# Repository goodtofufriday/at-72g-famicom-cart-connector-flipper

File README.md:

at-72g famicom cart connector flipper

for famiclones with the board labled at-72g. probably useable in similar famiclones.

If youre looking here i imagine you know how to mod consoles so i wont go through the how to.

this system doesnt connect expansion audio, so i added through hole pins for pin 45 and 46 so that you can easily re-enable it. 

i havent tested this. but it should work. measurements are "super close". it may need a need shaving. unless its super off im not going to update this design. 

feel free to use the library. it is a full famiclone cart connector library for eagle that i made.

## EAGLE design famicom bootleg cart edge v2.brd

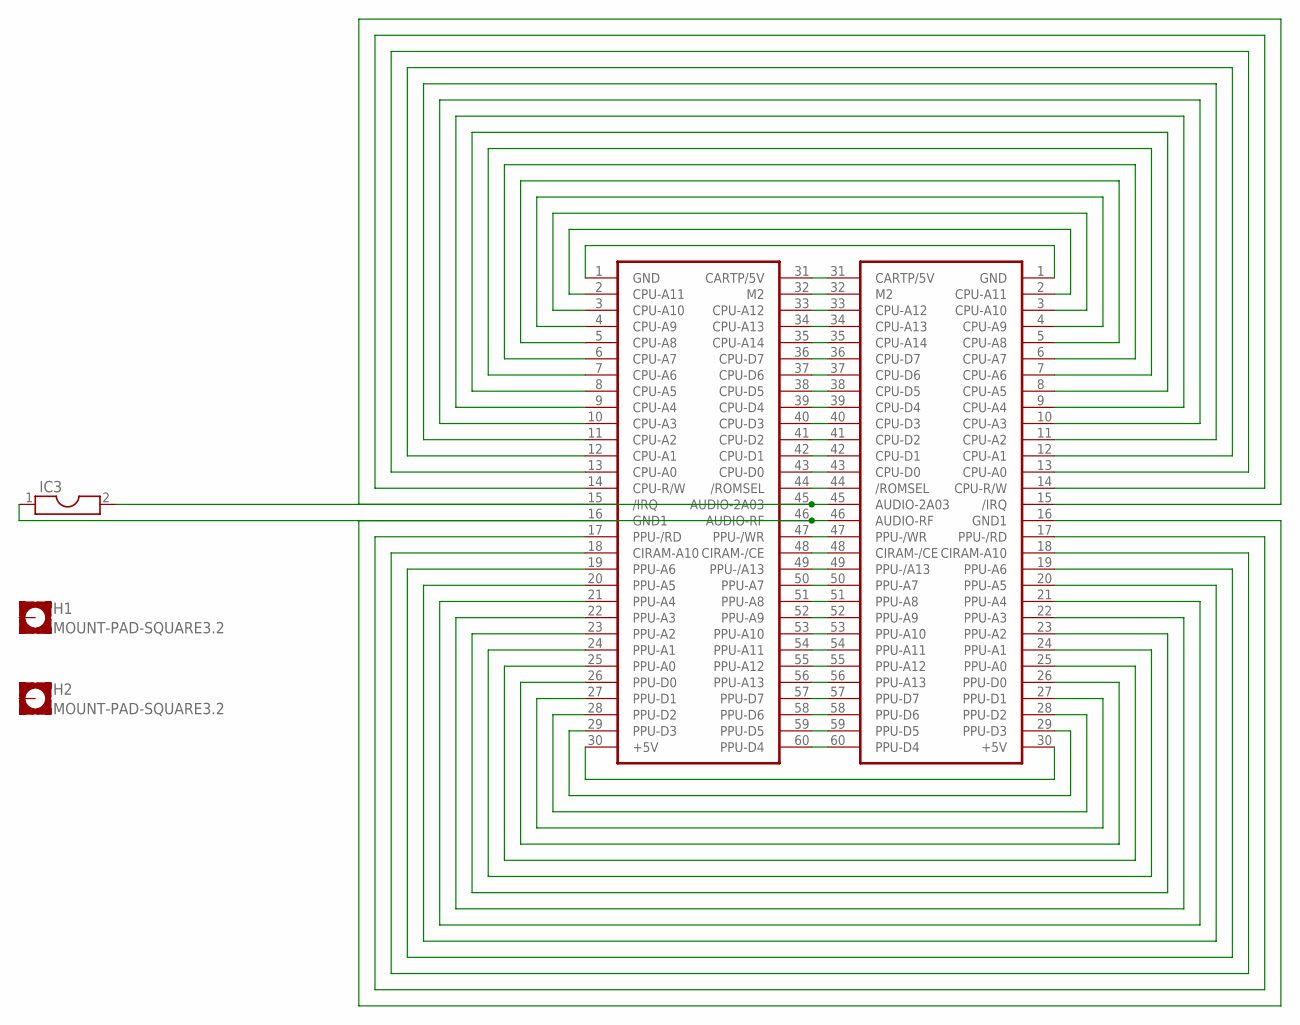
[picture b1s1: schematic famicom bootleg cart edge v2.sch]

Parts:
H1, H2: MOUNT-PAD-SQUARE3.2; 3,2-PAD-SQUARE
IC1, IC2: FAMICOM-CART-EDGE; DIL60
IC3: DIL2; DIL02

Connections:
unnamed: IC1.57 (PPU-D7), IC2.57 (PPU-D7)
unnamed: IC1.43 (CPU-D0), IC2.43 (CPU-D0)
unnamed: IC1.34 (CPU-A13), IC2.34 (CPU-A13)
unnamed: IC1.33 (CPU-A12), IC2.33 (CPU-A12)
unnamed: IC1.32 (M2), IC2.32 (M2)
unnamed: IC1.31 (CARTP/5V), IC2.31 (CARTP/5V)
unnamed: IC1.35 (CPU-A14), IC2.35 (CPU-A14)
unnamed: IC1.42 (CPU-D1), IC2.42 (CPU-D1)
unnamed: IC1.41 (CPU-D2), IC2.41 (CPU-D2)
unnamed: IC1.40 (CPU-D3), IC2.40 (CPU-D3)
unnamed: IC1.39 (CPU-D4), IC2.39 (CPU-D4)
unnamed: IC1.38 (CPU-D5), IC2.38 (CPU-D5)
unnamed: IC1.37 (CPU-D6), IC2.37 (CPU-D6)
unnamed: IC1.44 (/ROMSEL), IC2.44 (/ROMSEL)
unnamed: IC1.47 (PPU-/WR), IC2.47 (PPU-/WR)
unnamed: IC1.48 (CIRAM-/CE), IC2.48 (CIRAM-/CE)
unnamed: IC1.36 (CPU-D7), IC2.36 (CPU-D7)
unnamed: IC1.60 (PPU-D4), IC2.60 (PPU-D4)
unnamed: IC1.59 (PPU-D5), IC2.59 (PPU-D5)
unnamed: IC1.58 (PPU-D6), IC2.58 (PPU-D6)
unnamed: IC1.50 (PPU-A7), IC2.50 (PPU-A7)
unnamed: IC1.51 (PPU-A8), IC2.51 (PPU-A8)
unnamed: IC1.52 (PPU-A9), IC2.52 (PPU-A9)
unnamed: IC1.54 (PPU-A11), IC2.54 (PPU-A11)
unnamed: IC1.55 (PPU-A12), IC2.55 (PPU-A12)
unnamed: IC1.56 (PPU-A13), IC2.56 (PPU-A13)
unnamed: IC1.49 (PPU-/A13), IC2.49 (PPU-/A13)
unnamed: IC1.53 (PPU-A10), IC2.53 (PPU-A10)
unnamed: IC1.1 (GND), IC2.1 (GND)
unnamed: IC1.2 (CPU-A11), IC2.2 (CPU-A11)
unnamed: IC1.3 (CPU-A10), IC2.3 (CPU-A10)
unnamed: IC1.4 (CPU-A9), IC2.4 (CPU-A9)
unnamed: IC1.5 (CPU-A8), IC2.5 (CPU-A8)
unnamed: IC1.6 (CPU-A7), IC2.6 (CPU-A7)
unnamed: IC1.7 (CPU-A6), IC2.7 (CPU-A6)
unnamed: IC1.8 (CPU-A5), IC2.8 (CPU-A5)
unnamed: IC1.9 (CPU-A4), IC2.9 (CPU-A4)
unnamed: IC1.10 (CPU-A3), IC2.10 (CPU-A3)
unnamed: IC1.11 (CPU-A2), IC2.11 (CPU-A2)
unnamed: IC1.12 (CPU-A1), IC2.12 (CPU-A1)
unnamed: IC1.13 (CPU-A0), IC2.13 (CPU-A0)
unnamed: IC1.14 (CPU-R/W), IC2.14 (CPU-R/W)
unnamed: IC1.15 (/IRQ), IC2.15 (/IRQ)
unnamed: IC1.30 (+5V), IC2.30 (+5V)
unnamed: IC1.29 (PPU-D3), IC2.29 (PPU-D3)
unnamed: IC1.28 (PPU-D2), IC2.28 (PPU-D2)
unnamed: IC1.27 (PPU-D1), IC2.27 (PPU-D1)
unnamed: IC1.26 (PPU-D0), IC2.26 (PPU-D0)
unnamed: IC1.25 (PPU-A0), IC2.25 (PPU-A0)
unnamed: IC1.24 (PPU-A1), IC2.24 (PPU-A1)
unnamed: IC1.23 (PPU-A2), IC2.23 (PPU-A2)
unnamed: IC1.22 (PPU-A3), IC2.22 (PPU-A3)
unnamed: IC1.21 (PPU-A4), IC2.21 (PPU-A4)
unnamed: IC1.20 (PPU-A5), IC2.20 (PPU-A5)
unnamed: IC1.19 (PPU-A6), IC2.19 (PPU-A6)
unnamed: IC1.18 (CIRAM-A10), IC2.18 (CIRAM-A10)
unnamed: IC1.17 (PPU-/RD), IC2.17 (PPU-/RD)
unnamed: IC1.16 (GND1), IC2.16 (GND1)
PIN45: IC1.46 (AUDIO-RF), IC2.46 (AUDIO-RF), IC3.1
PIN46: IC1.45 (AUDIO-2A03), IC2.45 (AUDIO-2A03), IC3.2

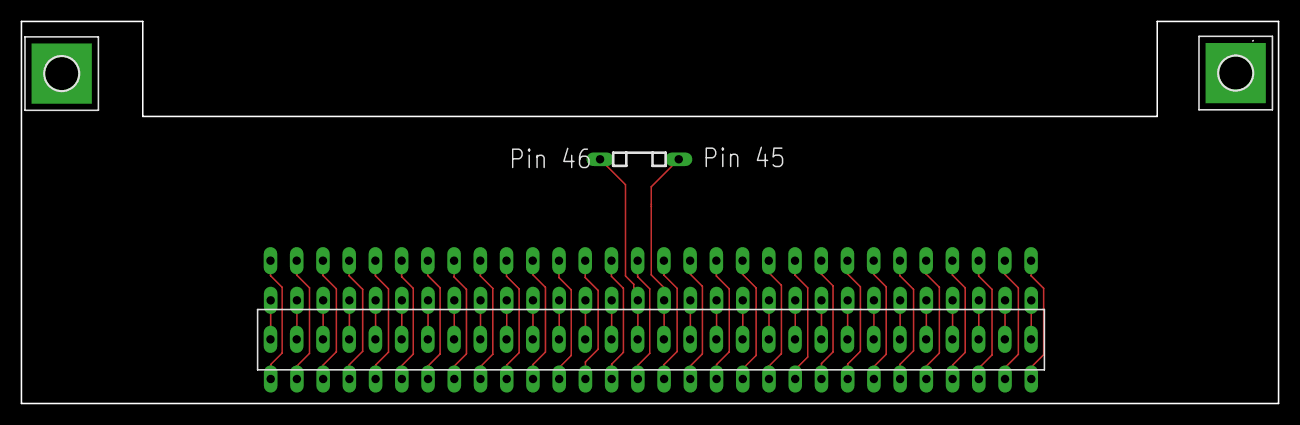
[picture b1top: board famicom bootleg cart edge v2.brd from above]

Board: 2 copper layers, 121.8 x 37.0 mm, 5 parts (1 on the bottom side), 60 nets.
